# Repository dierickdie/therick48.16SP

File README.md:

# therick48.16SP

SP = Southpaw

A 4x12 + 4x4 (48.16) ortho keyboard with USB C, SMD components, and 19mm spacing.

This is essentially a dumbed down Planck clone plus a southpaw numpad. The numpad is able to be snapped off to have just a 4x12.

If you want a regular side numpad, look at the [therick48.16](https://github.com/dierickdie/therick64BA). It uses the same firmware.

**Note: firmware is the same as therick48.16**

Although everything should<sup>(tm)</sup> work as is, it hasn't been physically tested.

**USE AT YOUR OWN RISK!!!** I am not responsible for any dumb things you do, fry your computer, break anything, etc.

## FAQ:
#### Does it have MIT/2x2u/etc.? 
No. Grid for life

#### Does it have backlighting?
No

#### Does it have RGB?
No

#### Does it have a rotary encoder?
~No~ Yep! There are 8 (lol) choices for location. However, only support for 2. Left and right.

#### Does it have hotswap?
No

#### Does it have Alps support?
No

#### Choc support?
No

#### Will you add any of these?
No

#### Why not?
I don't wanna

#### Will it fit a Planck case?
Yes! In theory. If you break off the numpad. Hasn't been tested.

#### Why USB C?
That's a dumb question

#### Will you add micro/mini/any USB other than type C?
No

#### Why not?
USB C is the future. Until a new standard comes out

#### But I don't have any USB C cables.
Boo hoo. I suggest building one. Zap Cables is a good place to get parts

#### Why is it named therick?
It started in fall of 2005 when I was just a boy. I started a new job, and needed a login name. The manager wrote The Rick (my first name is Rick). It has stuck ever since. Thanks, Sam! 64 is for 64 keys. Hope that was obvious.

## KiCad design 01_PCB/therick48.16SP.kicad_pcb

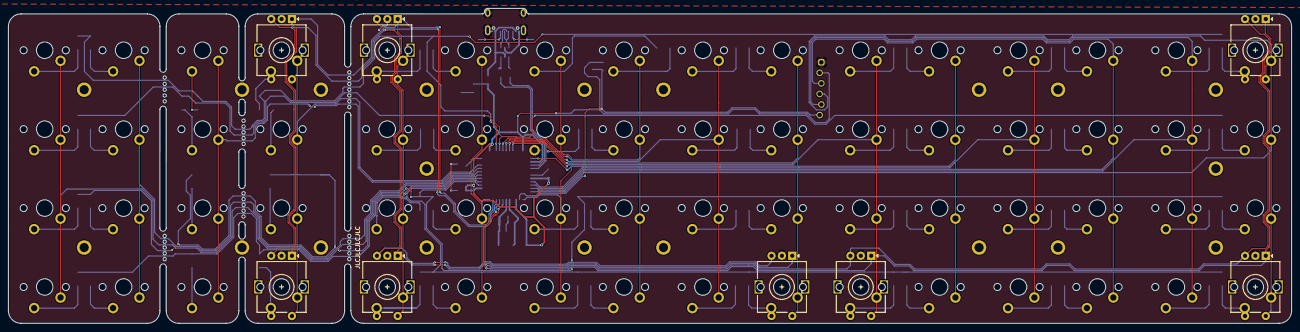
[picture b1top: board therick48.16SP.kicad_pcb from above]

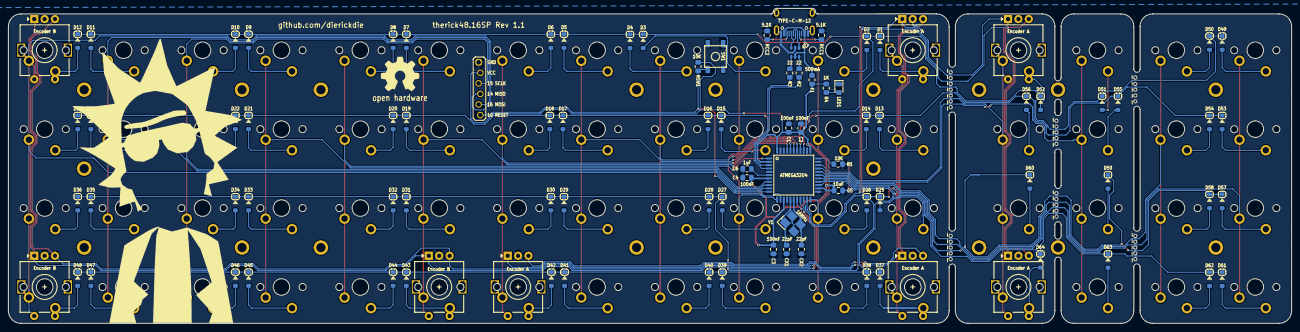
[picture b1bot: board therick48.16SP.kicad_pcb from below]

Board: 2 copper layers, 308.9 x 75.8 mm, 187 parts (89 on the bottom side), 105 nets.

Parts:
C1, C2, C3, C4: 100nF; C_0805_2012Metric_Pad1.15x1.40mm_HandSolder
C5: 10uF; C_0805_2012Metric_Pad1.15x1.40mm_HandSolder
C6: 1uF; C_0805_2012Metric_Pad1.15x1.40mm_HandSolder
CX1, CX2: 22pF; C_0805_2012Metric_Pad1.15x1.40mm_HandSolder
D1, D2, D3, D4, D5, D6, D7, D8, D9, D10, D11, D12, D13, D14, D15, D16, D17, D18, D19, D20, D21, D22, D23, D24, D25, D26, D27, D28, D29, D30, D31, D32, D33, D34, D35, D36, D37, D38, D39, D40, D41, D42, D43, D44, D45, D46, D47, D48, D49, D50, D51, D52, D53, D54, D55, D56, D57, D58, D59, D60, D61, D62, D63, D64: D; D_SOD-123_modified
F1: 500mA; Fuse_0805_2012Metric_Pad1.15x1.40mm_HandSolder
H1, H2, H3, H4, H5, H6, H7, H8, H9, H10, H11, H12, H13, H14, H15, H16, H17, H18, H19, H20: MountingHole; Generic-Mounthole
J1: TYPE-C-31-M12_13; TYPE-C-31-M-12
J2: AVR-ISP-6_mod; PIN_HEADER_1x6_OFFSET
K1, K2, K3, K4, K5, K6, K7, K8, K9, K10, K11, K12, K13, K14, K15, K16, K17, K18, K19, K20, K21, K22, K23, K24, K25, K26, K27, K28, K29, K30, K31, K32, K33, K34, K35, K36, K37, K38, K39, K40, K41, K42, K43, K44, K45, K46, K47, K48, K49, K50, K51, K52, K53, K54, K55, K56, K57, K58, K59, K60, K61, K62, K63, K64: KEYSW; MX100
LED1: LED; LED_0805_2012Metric_Pad1.15x1.40mm_HandSolder
R1: 10k; R_0805_2012Metric_Pad1.15x1.40mm_HandSolder
R2, R3: 22; R_0805_2012Metric_Pad1.15x1.40mm_HandSolder
R4: 1K; R_0805_2012Metric_Pad1.15x1.40mm_HandSolder
RCC1, RCC2: 5.1K; R_0805_2012Metric_Pad1.15x1.40mm_HandSolder
RSW1: 10k; R_0805_2012Metric_Pad1.15x1.40mm_HandSolder
SW1: SW_PUSH; SKQG-1155865
SW2, SW3, SW4, SW5, SW6, SW7, SW8, SW9: Rotary_Encoder_Switch; RotaryEncoder_EC11
U1: ATMEGA32U4; ATMEGA32U4-AU
U2: HOLE; rick_large
U3: USBLC6-2SC6; SOT-23-6
U4, U5, U6, U7, U10, U11: HOLE; MouseBite_IPC7351
U9: HOLE; OSHW-Logo2_14.6x12mm_SilkScreen
Y1: 16MHz; Crystal_SMD_3225-4Pin_3.2x2.5mm_HandSoldering

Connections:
D+: R3.2, U3.4
D+BUS: J1.A6, J1.B6, U3.3
D-: R2.2, U3.6
D-BUS: J1.A7, J1.B7, U3.1
EncA: SW2.A, SW3.A, SW4.A, SW5.A, SW8.A, U1.21
EncB: SW2.B, SW3.B, SW4.B, SW5.B, SW8.B, U1.20
EncC: SW6.A, SW7.A, SW9.A, U1.19
EncD: SW6.B, SW7.B, SW9.B, U1.18
GND: C1.2, C2.2, C3.2, C4.2, C5.2, C6.2, CX1.2, CX2.2, J1.A1, J1.B1, J1.S, J2.6, LED1.1, R1.1, RCC1.1, RCC2.1, SW1.1, SW2.C, SW3.C, SW4.C, SW5.C, SW6.C, SW7.C, SW8.C, SW9.C, U1.5, U1.15, U1.23, U1.35, U1.43, U3.2, Y1.2, Y1.4
ISP_Reset: J2.1, RSW1.1, SW1.2, U1.13
unnamed: C6.1, U1.6
unnamed: D1.2, K1.2, SW3.S1
unnamed: D2.2, K2.2
unnamed: D3.2, K3.2
unnamed: D4.2, K4.2
unnamed: D5.2, K5.2
unnamed: D6.2, K6.2
unnamed: D7.2, K7.2
unnamed: D8.2, K8.2
unnamed: D9.2, K9.2
unnamed: D10.2, K10.2
unnamed: D11.2, K11.2
unnamed: D12.2, K12.2, SW7.S1
unnamed: D13.2, K13.2
unnamed: D14.2, K14.2
unnamed: D15.2, K15.2
unnamed: D16.2, K16.2
unnamed: D17.2, K17.2
unnamed: D18.2, K18.2
unnamed: D19.2, K19.2
unnamed: D20.2, K20.2
unnamed: D21.2, K21.2
unnamed: D22.2, K22.2
unnamed: D23.2, K23.2
unnamed: D24.2, K24.2
unnamed: D25.2, K25.2
unnamed: D26.2, K26.2
unnamed: D27.2, K27.2
unnamed: D28.2, K28.2
unnamed: D29.2, K29.2
unnamed: D30.2, K30.2
unnamed: D31.2, K31.2
unnamed: D32.2, K32.2
unnamed: D33.2, K33.2
unnamed: D34.2, K34.2
unnamed: D35.2, K35.2
unnamed: D36.2, K36.2
unnamed: D37.2, K37.2, SW5.S1
unnamed: D38.2, K38.2
unnamed: D39.2, K39.2
unnamed: D40.2, K40.2
unnamed: D41.2, K41.2
unnamed: D42.2, K42.2, SW8.S1
unnamed: D43.2, K43.2, SW9.S1
unnamed: D44.2, K44.2
unnamed: D45.2, K45.2
unnamed: D46.2, K46.2
unnamed: D47.2, K47.2
unnamed: D48.2, K48.2, SW6.S1
unnamed: D49.2, K49.2
unnamed: D50.2, K50.2
unnamed: D51.2, K51.2
unnamed: D52.2, K52.2, SW2.S1
unnamed: D53.2, K53.2
unnamed: D54.2, K54.2
unnamed: D55.2, K55.2
unnamed: D56.2, K56.2
unnamed: D57.2, K57.2
unnamed: D58.2, K58.2
unnamed: D59.2, K59.2
unnamed: D60.2, K60.2
unnamed: D61.2, K61.2
unnamed: D62.2, K62.2
unnamed: D63.2, K63.2
unnamed: D64.2, K64.2, SW4.S1
unnamed: J1.A5, RCC1.2
unnamed: J1.B5, RCC2.2
unnamed: LED1.2, R4.1
unnamed: R1.2, U1.33
unnamed: R2.1, U1.3
unnamed: R3.1, U1.4
VBUS: F1.2, J1.A4, J1.B4, U3.5
VCC: C1.1, C2.1, C3.1, C4.1, C5.1, F1.1, J2.2, R4.2, RSW1.2, U1.2, U1.7, U1.14, U1.24, U1.34, U1.44
XTAL1: CX1.1, U1.16, Y1.1
XTAL2: CX2.1, U1.17, Y1.3
col0: K1.1, K13.1, K25.1, K37.1, SW3.S2, SW5.S2, U1.27
col1: K2.1, K14.1, K26.1, K38.1, U1.22
col2: K3.1, K15.1, K27.1, K39.1, U1.12
col3: K4.1, K16.1, K28.1, K40.1, U1.38
col4: K5.1, K17.1, K29.1, K41.1, U1.39
col5: K6.1, K18.1, K30.1, K42.1, SW8.S2, U1.40
col6: K7.1, K19.1, K31.1, K43.1, SW9.S2, U1.41
col7: K8.1, K20.1, K32.1, K44.1, U1.1
col8: K9.1, K21.1, K33.1, K45.1, U1.8
col9: J2.5, K10.1, K22.1, K34.1, K46.1, U1.9
col10: J2.4, K11.1, K23.1, K35.1, K47.1, U1.10
col11: J2.3, K12.1, K24.1, K36.1, K48.1, SW6.S2, SW7.S2, U1.11
col12: K49.1, K53.1, K57.1, K61.1, U1.28
col13: K50.1, K54.1, K58.1, K62.1, U1.29
col14: K51.1, K55.1, K59.1, K63.1, U1.30
col15: K52.1, K56.1, K60.1, K64.1, SW2.S2, SW4.S2, U1.31
row0: D1.1, D2.1, D3.1, D4.1, D5.1, D6.1, D7.1, D8.1, D9.1, D10.1, D11.1, D12.1, D49.1, D50.1, D51.1, D52.1, U1.36
row1: D13.1, D14.1, D15.1, D16.1, D17.1, D18.1, D19.1, D20.1, D21.1, D22.1, D23.1, D24.1, D53.1, D54.1, D55.1, D56.1, U1.37
row2: D25.1, D26.1, D27.1, D28.1, D29.1, D30.1, D31.1, D32.1, D33.1, D34.1, D35.1, D36.1, D57.1, D58.1, D59.1, D60.1, U1.25
row3: D37.1, D38.1, D39.1, D40.1, D41.1, D42.1, D43.1, D44.1, D45.1, D46.1, D47.1, D48.1, D61.1, D62.1, D63.1, D64.1, U1.26

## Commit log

2020-02-08 Update some routing
2020-02-08 Align Switches
2020-02-23 Changed pins to make routing cleaner
2020-05-15 Remapped ISP Flash, added mounting holes
2020-05-16 Add reset hole
2020-05-16 Update schematic
2020-05-19 Added mounting holes
2020-05-23 Rename from therick64 to therick48.16
2020-05-23 Rename files
2020-05-23 Changed gap between 4X12 and 4X4 to .25 inches
2020-05-23 Changed a trace
2020-05-24 48+16SP to 48.16SP
2020-05-24 Change 48+16SP to 48.16SP
2020-05-25 Add power LED
2020-05-25 Update fp-info-cache
2020-05-30 New Gerber files
2020-06-03 Made 2 columns able to be broken away
2020-06-05 Added breakaway section, added rotary encoder support
2020-06-05 Update Gerbers
2020-06-06 New gerber
2020-06-21 Small aesthetic tweaks
2020-07-01 Added encoder
